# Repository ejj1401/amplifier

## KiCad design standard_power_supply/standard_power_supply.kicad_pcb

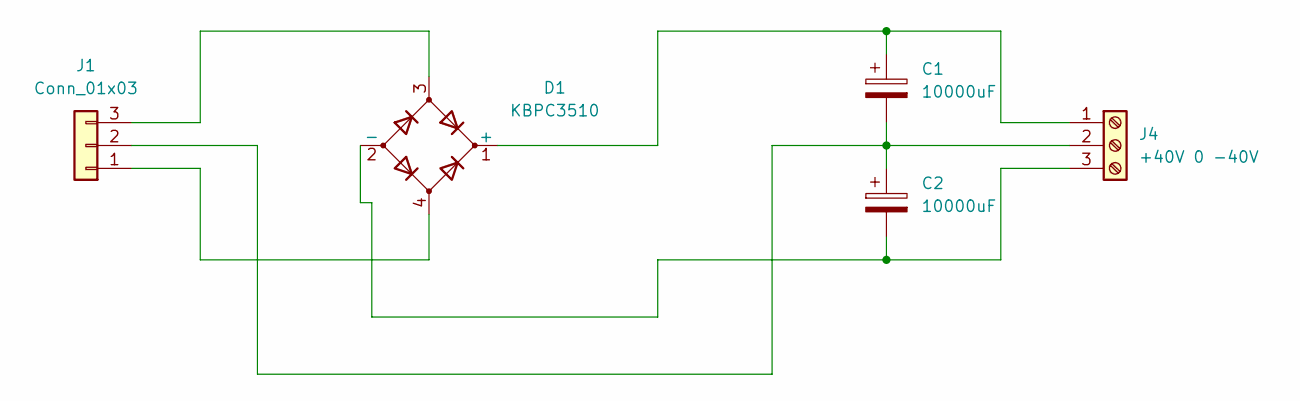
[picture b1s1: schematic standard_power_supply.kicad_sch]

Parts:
C1, C2: 10000uF; CP_Radial_D35.0mm_P10.00mm_SnapIn
D1: KBPC3510; Diode_Bridge_28.6x28.6x7.3mm_P18.0mm_P11.6mm
J1: Conn_01x03; TerminalBlock_Phoenix_MKDS-1,5-3-5.08_1x03_P5.08mm_Horizont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
J4: +40V 0 -40V; TerminalBlock_Phoenix_MKDS-1,5-3-5.08_1x03_P5.08mm_Horizont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

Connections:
unnamed: C1.1, D1.1 (+), J4.1
unnamed: C2.2, D1.2 (-), J4.3
unnamed: D1.4, J1.1
unnamed: C1.2, C2.1, J1.2, J4.2
unnamed: D1.3, J1.3

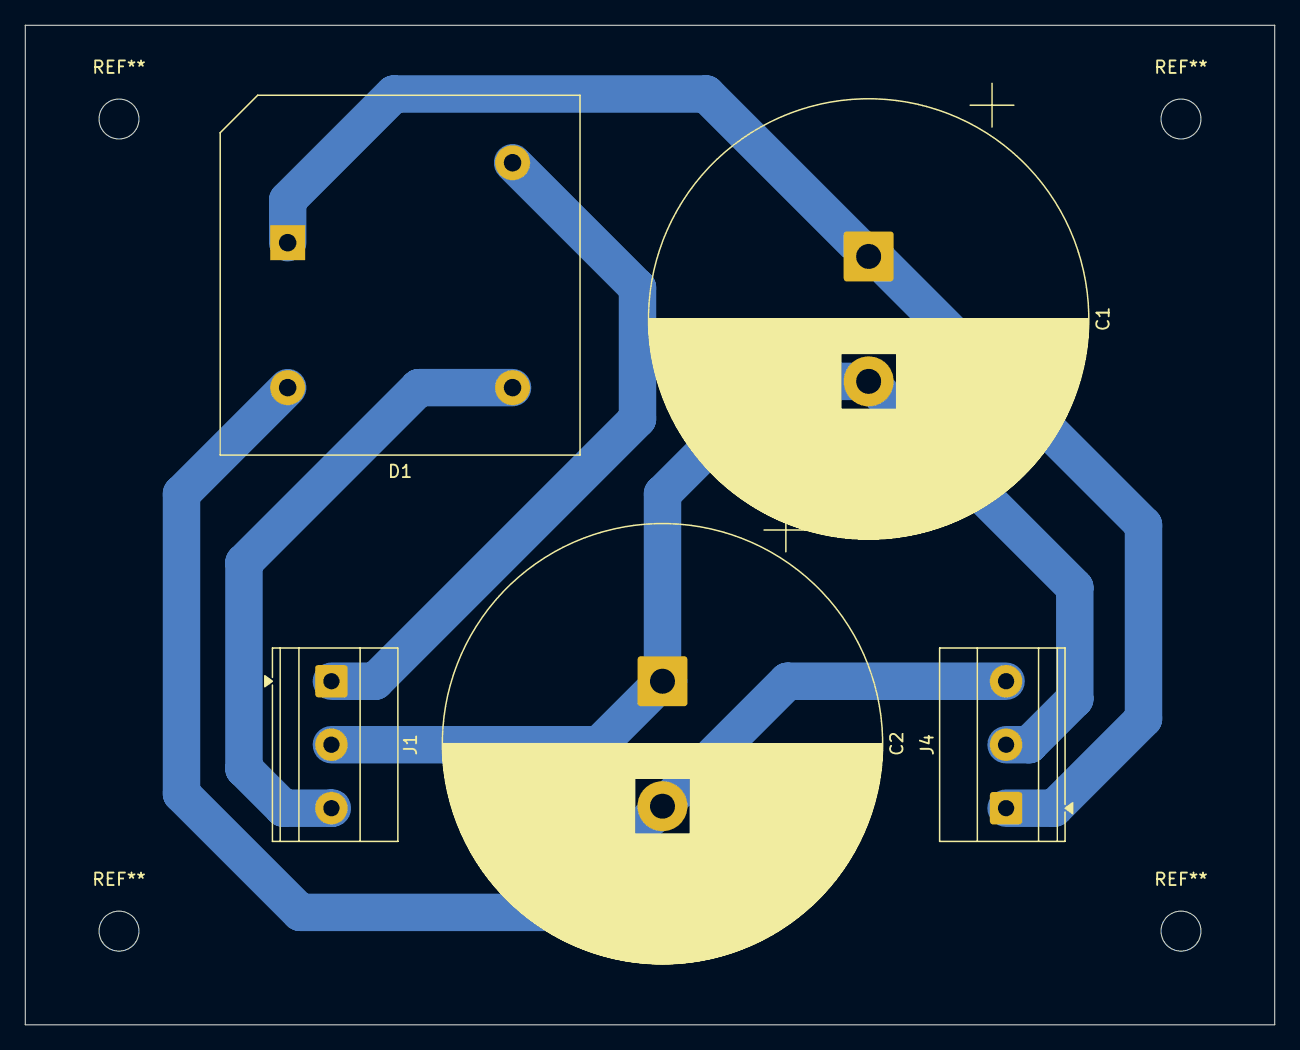
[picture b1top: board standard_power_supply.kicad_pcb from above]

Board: 2 copper layers, 100.0 x 80.0 mm, 5 parts (0 on the bottom side), 5 nets.

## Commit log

2026-02-02 Initial commit: Amplifier design and export.
2026-03-02 40V upgrade and generate BOM CSVs
2026-03-07 Finished PSU PCB Design
2026-03-07 Resolve 90 degree copper connection.
2026-03-07 Export printable copy for PCB design.
